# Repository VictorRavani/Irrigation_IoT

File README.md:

# Irrigation_IoT

Este projeto abrange o desenvolvimento completo de Hardware e Firmware para controle em IoT. Oferece todas as informações e recursos necessários para que qualquer pessoa possa configurar o sistema de forma independente.

# Atualizações a serem feitas v2: 

- Leds dos optocopadores, como os Leds estão em série acaba não havendo corrente sulficinete para acionalos...
- Conversor USB serial CP2102 pode ser removido pois o ESP32-S3 possui interface USB.
- Troca do conector Micro USB para USB tipo C.
- Desing da PCB adaptadada para um case de mercado.
- Substituir botoões por um encoder rotativo.
- Deixar os demais GPIOS disponíveis para uso utilizando conectores KRE. (Obs.: Prever circuitos de proteção com optoacopladores).

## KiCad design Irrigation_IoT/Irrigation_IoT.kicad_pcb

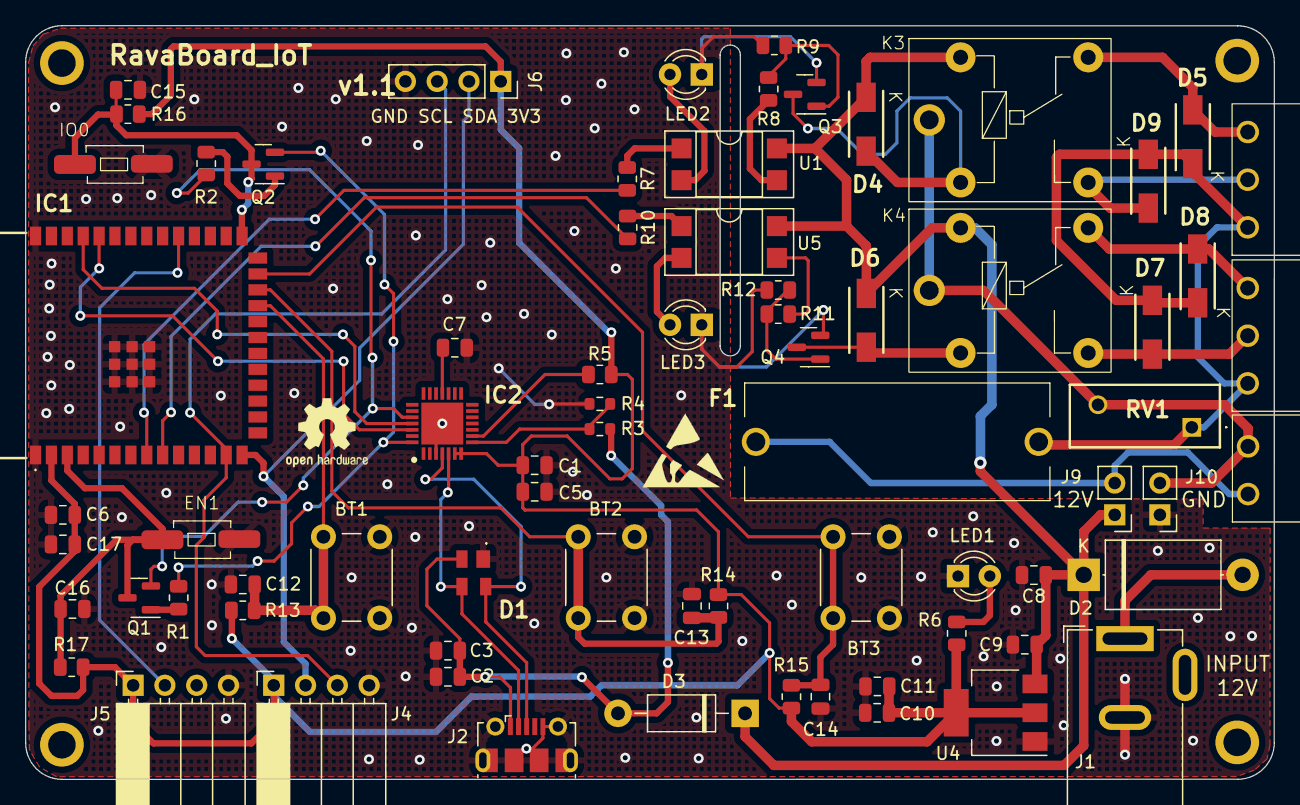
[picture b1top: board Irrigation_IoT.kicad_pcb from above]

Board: 2 copper layers, 99.8 x 60.2 mm, 73 parts (0 on the bottom side), 44 nets.

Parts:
BT1, BT2, BT3: SW_MEC_5G; SW_PUSH_6mm
C1: 4,7uF; C_0805_2012Metric
C2, C8, C10, C17: 10uF; C_0805_2012Metric
C3, C5, C6, C9, C11, C12, C13, C14, C15, C16: 100nF; C_0805_2012Metric
C7: 4.7uF; C_0805_2012Metric
D1: SP0503BAHTG
D2: SB560; D_DO-201AE_P12.70mm_Horizontal
D3: SB160; D_DO-41_SOD81_P10.16mm_Horizontal
D4, D5, D6, D7, D8, D9: 1N4007; Diodo_SM_DO-214
EN1: SW_MEC_5G; Chave Táctil Push Button SMD 2 Terminais 3x6x4,3 Preta (KFC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
F1: Fuse; Porta Fusível 5x20 AS-06
IC1: ESP32-S3-WROOM-1-N16R8; ESP32S3WROOM1N16R8
IC2: CP2102-GM; CP2102
IO0: SW_MEC_5G; Chave Táctil Push Button SMD 2 Terminais 3x6x4,3 Preta (KFC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
J1: Barrel_Jack_MountingPin; BarrelJack_GCT_DCJ200-10-A_Horizontal
J2: USB_B_Micro; USB_Micro-B_Molex-105017-0001
J3, J7: Screw_Terminal_01x03; BR7MN2 - BORNE RECEPTOR 90º PASSO 3,81MM METALTEX
J4: I2C Extern; PinSocket_1x04_P2.54mm_Horizontal
J5: Connector DHT22; PinSocket_1x04_P2.54mm_Horizontal
J6: Connector Display; PinSocket_1x04_P2.54mm_Vertical_DISPLAY_OLED
J8: Screw_Terminal_01x02; BR7MN2 - 2vias
J9, J10: Conn_12V; PinHeader_1x02_P2.54mm_Vertical
K3, K4: AX1RC2; MA1RC
LED1: FONT_ON; LED_D3.0mm
LED2, LED3: LED_VM; LED_D3.0mm
Q1, Q2, Q3, Q4: BC817; SOT-23
R1, R2, R5: 4K7; R_0805_2012Metric
R3: 24K; R_0603_1608Metric
R4: 47K; R_0603_1608Metric
R6, R7, R10: 220R; R_0805_2012Metric
R8, R11: 2K2; R_0805_2012Metric
R9, R12, R13, R14, R15, R16, R17: 10K; R_0805_2012Metric
RV1: Varistor; Varistor_B72210S0271K101
U1, U5: PC817; DIP-4_W7.62mm_SMDSocket_SmallPads
U4: LM1117DT-3.3; SOT-223-3_TabPin2

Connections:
+3.3V: C1.1, C5.1, C6.1, C10.1, C11.1, C17.1, IC1.2 (3V3), IC2.6 (VDD), IC2.7 (REGIN), J4.1, J5.1, J6.1, R5.2, R6.1, R13.1, R14.1, R15.1, R16.1, R17.1, U4.2 (VO)
+12V: C8.1, C9.1, D2.1 (K), D3.1 (K), D4.1 (K), D6.1 (K), J9.1, K3.5, K4.5, U1.4, U4.3 (VI), U5.4
/BT_1: BT1.1, C12.1, IC1.23 (IO21), R13.2
/BT_2: BT2.1, C13.1, IC1.24 (IO47), R14.2
/BT_3: BT3.1, C14.1, IC1.25 (IO48), R15.2
/D+: D1.4 (K_3), IC2.4 (D+), J2.3 (D+)
/D-: D1.3 (K_2), IC2.5 (D-), J2.2 (D-)
/DHT22_SDA: IC1.31 (IO38), J5.2
/DTR: IC2.28 (DTR), Q2.2 (E), R1.1
/EN: C16.1, EN1.1, IC1.3 (EN), Q1.3 (C), R17.2
/ESP_RX: IC1.36 (RXD0), IC2.26 (TXD)
/ESP_TX: IC1.37 (TXD0), IC2.25 (RXD)
/IO0: C15.1, IC1.27 (IO0), IO0.1, Q2.3 (C), R16.2
/RELE_1: IC1.8 (IO15), R7.2
/RELE_2: IC1.9 (IO16), R10.2
/RTS: IC2.24 (RTS), Q1.2 (E), R2.1
/SCL: IC1.13 (IO19), J4.3, J6.3
/SDA: IC1.14 (IO20), J4.2, J6.2
/VBUS: C2.1, C3.1, D1.2 (K_1), D3.2 (A), J2.1 (VBUS), R3.1
Earth: BT1.2, BT2.2, BT3.2, C1.2, C2.2, C3.2, C5.2, C6.2, C7.2, C8.2, C9.2, C10.2, C11.2, C12.2, C13.2, C14.2, C15.2, C16.2, C17.2, D1.1 (COMMON_A), EN1.2, IC1.1 (GND_1), IC1.40 (GND_2), IC1.41 (GND_3), IC1.42 (GND_4), IC1.43 (GND_5), IC1.44 (GND_6), IC1.45 (GND_7), IC1.46 (GND_8), IC1.47 (GND_9), IC1.48 (GND_10), IC1.49 (GND_11), IC2.3 (GND_1), IC2.29 (GND_2), IO0.2, J1.2, J2.5 (GND), J2.6 (Shield), J4.4, J5.4, J6.4, J10.1, LED1.1 (K), LED2.1 (K), LED3.1 (K), Q3.2 (E), Q4.2 (E), R4.1, R9.2, R12.2, U4.1 (GND)
unnamed: D2.2 (A), J1.1
unnamed: D4.2 (A), K3.1, Q3.3 (C)
unnamed: D5.2 (A), J3.2, K3.3
unnamed: D5.1 (K), D7.1 (K), D8.1 (K), D9.1 (K), F1.1, J3.1, J7.1, RV1.1
unnamed: D6.2 (A), K4.1, Q4.3 (C)
unnamed: D7.2 (A), J7.2, K4.3
unnamed: D8.2 (A), J7.3, K4.4
unnamed: D9.2 (A), J3.3, K3.4
unnamed: C7.1, IC2.18 (NC/VPP)
unnamed: IC2.8 (VBUS), R3.2, R4.2
unnamed: IC2.9 (~RST), R5.1
unnamed: F1.2, J8.1, J9.2
unnamed: J8.2, J10.2, K3.2, K4.2, RV1.2
unnamed: LED1.2 (A), R6.2
unnamed: LED2.2 (A), U1.2
unnamed: LED3.2 (A), U5.2
unnamed: Q1.1 (B), R1.2
unnamed: Q2.1 (B), R2.2
unnamed: Q3.1 (B), R8.1
unnamed: Q4.1 (B), R11.1, R12.1
unnamed: R7.1, U1.1
unnamed: R8.2, R9.1, U1.3
unnamed: R10.1, U5.1
unnamed: R11.2, U5.3

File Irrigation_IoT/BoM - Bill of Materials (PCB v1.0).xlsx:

Bill of Materials
Company Name:
Project Name:
Date:
RESISTORS
ID | Qty. | Qty. * 4 | Part Designator | Manufacturer Number | Description
1 |  | 0 | R1, R9, R12, R13, R14, R15, R16, R17, |  | Resistor SMD 10K 0805 5%
2 |  | 0 | R8, R11 |  | Resistor SMD 2K2 0805 5%
3 |  | 0 | R2, R5 |  | Resistor SMD 4K7 0805 5%
4 |  | 0 | R3 |  | Resistor SMD 24K 0603 1%
5 |  | 0 | R4 |  | Resistor SMD 47K 0603 1%
6 |  | 0 | R6, R7, R10 |  | Resistor SMD 220R 0805 5%
CAPACITORS
ID | Qty. | Qty. | Part Designator | Manufacturer Number | Description
1 | 2 | 8 | C1, C7 |  | Capacitor Cerâmico SMD 4,7uF 0805 25V
2 | 9 | 36 | C2, C8, C10, C17 |  | Capacitor Cerâmico SMD 10uF 0805 25V
3 | 2 | 8 | C3, C5, C6, C9, C11, C12, C13, C14, C15, C16 |  | Capacitor Cerâmico SMD 100nF 0805 50V
INDUCTORS
ID | Qty. | Qty. | Part Designator | Manufacturer Number | Description
 |  | 0
OSCILLATORS
ID | Qty. | Qty. | Part Designator | Manufacturer Number | Description
 |  | 0
TRANSISTORS
ID | Qty. | Qty. | Part Designator | Manufacturer Number | Description
 |  | 0 | Q3, Q4 |  | BC817 NPN
PROTECTION DEVICES
ID | Qty. | Qty. | Part Designator | Manufacturer Number | Description
 |  | 2 | RV1 (DNP) | MOV-10D431KTR | Varistor 10K AC 275V
DIODES
ID | Qty. | Qty. | Part Designator | Manufacturer Number | Description
 |  | 0 | D1 |  | Diodo Supressor SP0503BAHTG SOT
 |  | 0
INTREGRATED CIRCUITS
ID | Qty. | Qty. | Part Designator | Manufacturer Number | Description
 |  |  | U1, U5 |  | EL817/PC817 ISOLADOR ÓPTICO SMD
 |  |  | IC1 |  | Módulo Esp32-s3 - Esp32-s3-wroom-1 N16r8
 |  |  | IC2 |  | Circuito Integrado CP2102-GMR SMD QFN-28
 |  | 0 | U1 |  | LM1117DTX-3.3 - 3.3V SMD
ELECTROMECHANICS
ID | Qty. | Qty. | Part Designator | Manufacturer Number | Description
1 | 2 | 8 | K3, K4 | MA1RC2 (Metaltex) | Miniature relay AX1RC2
CONNECTORS
ID | Qty. | Qty. | Part Designator | Manufacturer Number | Description
1 |  |  | J1 |  | CONECTOR JACK DC-005 J4, 3T 2,1MM
2 |  |  | J2 |  | CONECTOR USB MICRO-B
3 |  |  | J3, J7 |  | BR7F2-03
4 |  |  | J8 |  | BR7F2-02
5 |  |  | J3, J7 |  | BR7MN2-03
6 |  |  | J8 |  | BR7MN2-02
7
8
9
OTHERS
ID | Qty. | Qty. | Part Designator | Manufacturer Number | Description
 |  | 2 | IO0, EN |  | CHAVE TÁCTIL 3X6X4,3 SMD 2 TERMINAIS
 |  | 4 | BT1, BT2, BT3 |  | CHAVE TÁCTIL 6X6x15 4 TERMINAIS PT

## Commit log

2024-07-29 Frist commit
2024-07-29 Merge
2024-07-29 Inclusão do step
2024-08-09 atualização de arquivos
